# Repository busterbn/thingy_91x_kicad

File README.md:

# Thingy:91 X in KiCad

KiCad 10 port of Nordic's Thingy:91 X hardware files (v2.0.0), converted from the original Altium project.

- `pca20065/` main board (PCA20065 v2.0.0)
- `pca64165/` current measurement and debug board (PCA64165 v1.1.0)
- `casing/` enclosure STEP files
- `tools/` scripts used for the conversion

Open the `.kicad_pro` files in KiCad 10 or newer. Footprints, symbols and 3D models are included in the project folders.

## Notes

Schematic and PCB connectivity was checked pin by pin against the original Altium board, and they match.

Altium harnesses are now KiCad bus groups, so some nets were renamed, e.g. `BMI270_INT` is `INTERRUPT.INT2`.

Nordic's design rules are in the `.kicad_dru` files. DRC still shows some warnings that come from the original design (stacked vias, a few 0.09 mm clearances around the nRF5340, silkscreen).

`kicad-cli` schematic parity reports "No corresponding pin" for unlabeled nets. Update PCB from Schematic in the GUI shows no changes, so this looks like a CLI issue.

3D models missing from Nordic's files were added in `pca20065/3dmodels/`: nRF9151 from SnapMagic, most passives/RF parts from LCSC/EasyEDA, the tactile switch from the LanguidSmartass/altium-libs repo, and generic side-view LED and WSON-8 models from the KiCad library. The nPM6001 and nRF5340 (WLCSP) still have no model.

## License

The design is Nordic Semiconductor's. See `License.txt` and `Legal_Disclaimer.pdf`. This is not an official Nordic release.

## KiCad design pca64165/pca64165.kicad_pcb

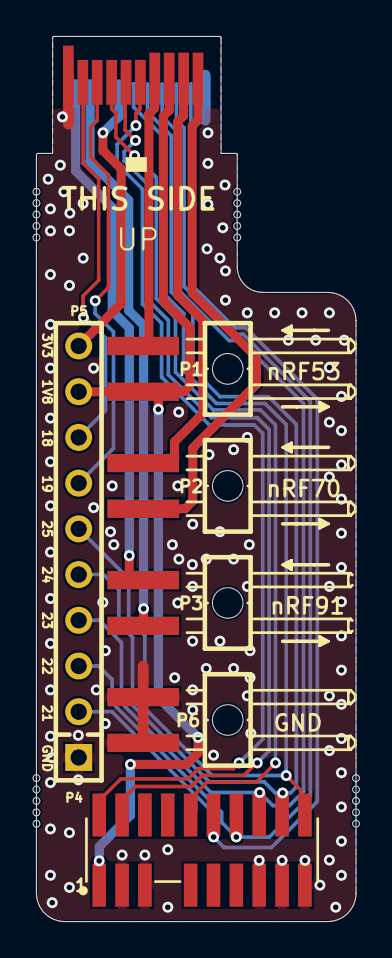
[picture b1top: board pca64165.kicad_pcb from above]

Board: 2 copper layers, 17.8 x 49.2 mm, 10 parts (0 on the bottom side), 18 nets.

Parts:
J2: Card Edge, 0.8mm; 10056847-101LF_Mating_Board_Thingy91_v2
JP1, JP2, JP3: Shunt 2.54mm; Shunt_2.54mm_Horizontal
P1, P2, P3, P6: Pin List 1x2, Angled; LIST_ANG_1x2-SMD-2.54MM
P4: Pin Header 2x10, 1.27mm, SWD; HDR_2x10-SMD-1.27mm-K-SWD
P5: Pin List 1x10; LIST_1x10-NC

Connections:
3V3: J2.14, P5.10
/P0.18: J2.9, P5.8
/P0.19: J2.8, P5.7
/P0.21: J2.19, P4.12, P5.2
/P0.22: J2.18, P4.14, P5.3
/P0.23: J2.17, P4.16, P5.4
/P0.24: J2.16, P4.18, P5.5
/P0.25: J2.15, P4.20, P5.6
/RESET: J2.7, P4.10
/SWDCLK: J2.6, P4.4
/SWDIO: J2.5, P4.2
GND: J2.10, J2.20, P4.3, P4.5, P4.15, P4.17, P4.19, P5.1, P6.1, P6.2
nRF53_VIN: J2.3, P1.1, P4.1, P5.9
nRF53_VOUT: J2.4, P1.2
nRF70_VIN: J2.1, P2.1
nRF70_VOUT: J2.2, P2.2
nRF91_VIN: J2.12, P3.1
nRF91_VOUT: J2.11, P3.2
